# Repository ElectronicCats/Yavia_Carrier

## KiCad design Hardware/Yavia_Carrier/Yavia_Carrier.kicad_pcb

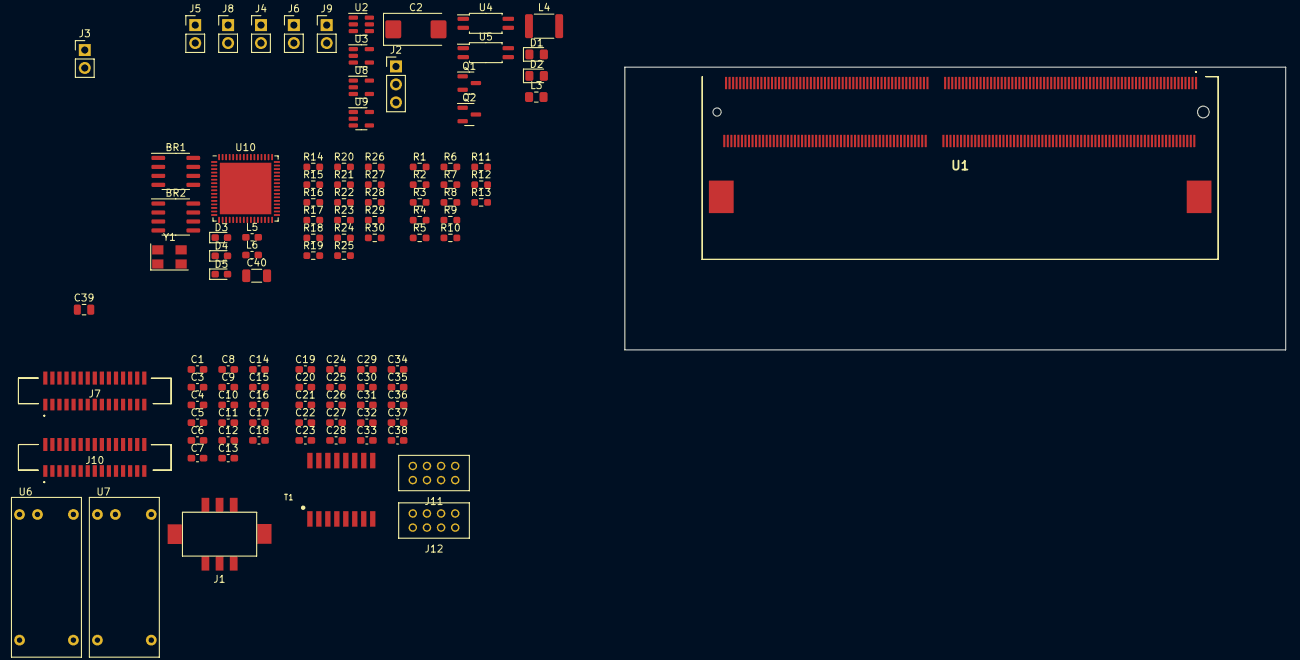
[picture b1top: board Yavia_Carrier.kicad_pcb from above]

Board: 2 copper layers, 93.5 x 40.0 mm, 107 parts (0 on the bottom side), 92 nets, no tracks yet.

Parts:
BR1, BR2: SP4031; SOIC-8_3.9x4.9mm_P1.27mm
C1, C3, C4, C5, C8, C11, C12: 22uF; C_0603_1608Metric_Pad1.08x0.95mm_HandSolder
C2: 220uF; CP_EIA-7343-31_Kemet-D_Pad2.25x2.55mm_HandSolder
C6, C7, C10: 10uF; C_0603_1608Metric_Pad1.08x0.95mm_HandSolder
C9: 100nF; C_0603_1608Metric_Pad1.08x0.95mm_HandSolder
C13, C14, C15, C16, C17, C18, C19, C21, C22, C23, C24, C25, C26, C28, C29, C31, C32, C33, C35, C36, C38: 0.1uF; C_0603_1608Metric_Pad1.08x0.95mm_HandSolder
C20: 4.7uF; C_0603_1608Metric_Pad1.08x0.95mm_HandSolder
C27, C34: 33pF; C_0603_1608Metric_Pad1.08x0.95mm_HandSolder
C30: 0.01uF; C_0603_1608Metric_Pad1.08x0.95mm_HandSolder
C37: 1uF; C_0603_1608Metric_Pad1.08x0.95mm_HandSolder
C39: 0.022uF; C_0805_2012Metric
C40: 1000pF; C_1206_3216Metric
D1: 5v; LED_0805_2012Metric_Pad1.15x1.40mm_HandSolder
D2: User; LED_0805_2012Metric_Pad1.15x1.40mm_HandSolder
D3, D4, D5: LED_Small; LED_0603_1608Metric_Pad1.05x0.95mm_HandSolder
J1: Power; DF11CZ-6DP-2V
J2: Serial; PinHeader_1x03_P2.54mm_Vertical
J3, J4: STRB_IS; PinHeader_1x02_P2.54mm_Vertical
J5, J6: STRB; PinHeader_1x02_P2.54mm_Vertical
J7, J10: 52610-1572; 526101572
J8, J9: FLASH; PinHeader_1x02_P2.54mm_Vertical
J11: USB; DF11-8DP-2DSA(08)
J12: Ethernet; DF11-8DP-2DSA(08)
L3: 2.2uH; L_0805_2012Metric_Pad1.15x1.40mm_HandSolder
L4: 3.9uH; L_1812_4532Metric
L5, L6: 2A_120R_100MHz; L_0603_1608Metric_Pad1.05x0.95mm_HandSolder
Q1, Q2: MMBT2222ALT1G; SOT-23
R1, R3, R6, R7, R10, R11, R16, R17, R18: 1K; R_0603_1608Metric_Pad0.98x0.95mm_HandSolder
R2: 10m; R_0603_1608Metric_Pad0.98x0.95mm_HandSolder
R4, R5: 4.7K; R_0603_1608Metric_Pad0.98x0.95mm_HandSolder
R8, R9: 500K; R_0603_1608Metric_Pad0.98x0.95mm_HandSolder
R12, R13, R14, R19, R23: 10K; R_0603_1608Metric_Pad0.98x0.95mm_HandSolder
R15: 1M; R_0603_1608Metric_Pad0.98x0.95mm_HandSolder
R20: 10R; R_0603_1608Metric_Pad0.98x0.95mm_HandSolder
R21, R22, R26, R28: 50R; R_0603_1608Metric_Pad0.98x0.95mm_HandSolder
R24: 12.0K 1/10W; R_0603_1608Metric_Pad0.98x0.95mm_HandSolder
R25: 825 1/10W; R_0603_1608Metric_Pad0.98x0.95mm_HandSolder
R27: 12.4K; R_0603_1608Metric_Pad0.98x0.95mm_HandSolder
R29, R30: 75R; R_0603_1608Metric_Pad0.98x0.95mm_HandSolder
T1: HX1188NL; HXXXX
U1: Verdin iMX8M Plus; 23094092
U2: AP63203; TSOT-23-6
U3: LM3671; SOT-23-5
U4, U5: TCMT1103; SOP-4_4.4x2.6mm_P1.27mm
U6, U7: LDD600L; LDD-L
U8, U9: 74AHC1G32; SOT-23-5
U10: LAN9512i; QFN-64-1EP_9x9mm_P0.5mm_EP7.3x7.3mm
Y1: 25MHZ; Crystal_SMD_5032-4Pin_5.0x3.2mm

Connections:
+1V8: C10.1, C14.1, L3.2, U3.4 (ADJ)
+3V3: C11.1, C12.1, C13.1, C15.1, C17.1, C18.1, C19.1, C21.1, C24.1, C28.1, C32.1, D1.2 (A), J7.1, J7.2, J10.1, L4.2, L5.1, R4.2, R5.2, R8.1, R9.1, R14.2, R16.1, R17.1, R18.1, R19.2, R23.2, R25.2, U2.1 (FB), U8.5 (VCC), U9.5 (VCC), U10.19 (VDD33IO), U10.27 (VDD33IO), U10.28 (~TRST), U10.29 (TMS), U10.30 (TDI), U10.33 (VDD33IO), U10.39 (VDD33IO), U10.40 (TEST3), U10.46 (VDD33IO)
+5V: C2.1, C6.1, C7.1, C16.1, J1.5, J11.2, J11.4, U2.2 (EN), U2.3 (VIN), U3.1 (VIN), U3.3 (EN)
+12V: J1.1, R12.1, R13.1, U6.1 (VIN+), U7.1 (VIN+)
+36V: J8.1, J9.1, U6.6 (+VOUT), U7.6 (+VOUT)
/CAM0_CLK+: J10.13, U1.162 (CSI2_CLK_P)
/CAM0_CLK-: J10.15, U1.160 (CSI2_CLK_N)
/CAM0_D0+: J10.25, U1.150 (CSI2_D0_P)
/CAM0_D0-: J10.27, U1.148 (CSI2_D0_N)
/CAM0_D1+: J10.19, U1.156 (CSI2_D1_P)
/CAM0_D1-: J10.21, U1.154 (CSI2_D1_N)
/CAM0_IO0: J10.9, U1.216 (GPIO_5)
/CAM0_IO1: J10.7, U1.218 (GPIO_6)
/CAM0_SCL: J10.5, U1.14 (I2C_1_SCL)
/CAM0_SDA: J10.3, U1.12 (I2C_1_SDA)
/CAM1_CLK+: J7.13, J7.14, U1.111 (CSI_1_CLK_P)
/CAM1_CLK-: J7.15, J7.16, U1.113 (CSI_1_CLK_N)
/CAM1_D0+: J7.25, J7.26, U1.123 (CSI_1_D0_P)
/CAM1_D0-: J7.27, J7.28, U1.125 (CSI_1_D0_N)
/CAM1_D1+: J7.19, J7.20, U1.117 (CSI_1_D1_P)
/CAM1_D1-: J7.21, J7.22, U1.119 (CSI_1_D1_N)
/CAM1_IO0: J7.9, J7.10, U1.222 (GPIO_8)
/CAM1_IO1: J7.7, J7.8, U1.220 (GPIO_7)
/CAM1_SCL: J7.5, J7.6, R5.1, U1.93 (I2C_4_CSI_SDA)
/CAM1_SDA: J7.3, J7.4, R4.1, U1.95 (I2C_4_CSI_SCL)
/Flash_EN: U1.208 (GPIO_2), U8.2
/Flash_EN_1: U1.210 (GPIO_3), U9.2
/LDD_OUT: Q1.3 (C), R12.2, U6.3 (PWM)
/LDD_OUT_1: Q2.3 (C), R13.2, U7.3 (PWM)
/LED_R: D2.2 (A), U1.206 (GPIO_1)
/RX_UART: J2.2, U1.129 (UART_1_RXD)
/TX_UART: J2.1, U1.131 (UART_1_TXD)
/USB_ETHERNET/DRx+: J12.3, T1.11
/USB_ETHERNET/DRx-: J12.1, T1.9
/USB_ETHERNET/DS1_D+: J11.5, U10.2 (USBDP2)
/USB_ETHERNET/DS1_D-: J11.7, U10.1 (USBDM2)
/USB_ETHERNET/DS2_D+: J11.1, U10.4 (USBDP3)
/USB_ETHERNET/DS2_D-: J11.3, U10.3 (USBDM3)
/USB_ETHERNET/DTx+: J12.7, T1.16
/USB_ETHERNET/DTx-: J12.5, T1.14
/USB_ETHERNET/LED_FDX: D5.1 (K), U10.20 (~FDX_LED/GPIO0)
/USB_ETHERNET/LNKA_LED: D4.1 (K), U10.21 (~LNKA_LED/GPIO1)
/USB_ETHERNET/ORx+: BR1.5 (OUT), U10.52 (RXP)
/USB_ETHERNET/ORx-: BR1.8 (OUT), U10.53 (RXN)
/USB_ETHERNET/OTx+: BR2.5 (OUT), U10.55 (TXP)
/USB_ETHERNET/OTx-: BR2.8 (OUT), U10.56 (TXN)
/USB_ETHERNET/RST: C30.1, R14.1, U10.12 (~RESET)
/USB_ETHERNET/RX+: BR1.4 (IN), R26.1, T1.6
/USB_ETHERNET/RX-: BR1.1 (IN), R28.1, T1.8
/USB_ETHERNET/SPD_LED: D3.1 (K), U10.22 (~SPD_LED/GPIO2)
/USB_ETHERNET/TX+: BR2.4 (IN), R21.1, T1.1
/USB_ETHERNET/TX-: BR2.1 (IN), R22.1, T1.3
/USB_ETHERNET/VDD18: C20.1, C23.1, C26.1, U10.15 (VDD18CORE), U10.38 (VDD18CORE)
/USB_ETHERNET/VDD18E: C33.1, L6.1, U10.48 (VDD18ETHPLL)
/USB_ETHERNET/VDD18U: C37.1, L6.2, U10.62 (VDD18USBPLL)
/USB_ETHERNET/VDD33A: C22.1, C25.1, C29.1, C31.1, C35.1, C36.1, C38.1, L5.2, R20.2, R21.2, R22.2, R26.2, R28.2, U10.5 (VDD33A), U10.10 (VDD33A), U10.49 (VDD33A), U10.51 (VDD33A), U10.54 (VDD33A), U10.57 (VDD33A), U10.64 (VDD33A)
/USB_ETHERNET/XI: C27.1, R15.2, U10.61 (XI), Y1.1
/USB_ETHERNET/XO: C34.1, R15.1, U10.60 (XO), Y1.3
/VT: C1.1, C3.1, C4.1, C5.1, C8.1, R2.2, U1.251 (VCC), U1.253 (VCC), U1.255 (VCC), U1.257 (VCC), U1.259 (VCC)
/opto_out: J3.2, R8.2, U4.4, U8.1
/opto_out_1: J4.2, R9.2, U5.4, U9.1
GND: C1.2, C2.2, C3.2, C4.2, C5.2, C6.2, C7.2, C8.2, C10.2, C11.2, C12.2, C13.2, C14.2, C15.2, C16.2, C17.2, C18.2, C19.2, C20.2, C21.2, C22.2, C23.2, C24.2, C25.2, C26.2, C27.2, C28.2, C29.2, C30.2, C31.2, C32.2, C33.2, C34.2, C35.2, C36.2, C37.2, C38.2, C39.2, C40.2, J1.2, J1.3, J1.4, J1.6, J2.3, J3.1, J4.1, J7.11, J7.12, J7.17, J7.18, J7.23, J7.24, J7.29, J7.30, J10.11, J10.17, J10.23, J10.29, J11.6, J11.8, Q1.2 (E), Q2.2 (E), R1.2, R3.2, R24.2, R27.2, U1.10 (GND), U1.11 (GND), U1.18 (GND), U1.27 (GND), U1.28 (GND), U1.33 (GND), U1.39 (GND), U1.40 (GND), U1.45 (GND), U1.50 (GND), U1.51 (GND), U1.65 (GND), U1.68 (GND), U1.71 (GND), U1.77 (GND), U1.83 (GND), U1.86 (GND), U1.89 (GND), U1.97 (GND), U1.98 (GND), U1.103 (GND), U1.109 (GND), U1.110 (GND), U1.115 (GND), U1.121 (GND), U1.122 (GND), U1.127 (GND), U1.134 (GND), U1.145 (GND), U1.146 (GND), U1.158 (GND), U1.167 (GND), U1.170 (GND), U1.173 (GND), U1.179 (GND), U1.182 (GND), U1.194 (GND), U1.195 (GND), U1.204 (GND), U1.209 (GND), U1.223 (GND), U1.224 (GND), U1.229 (GND), U1.230 (GND), U1.236 (GND), U1.242 (GND), U1.243 (GND), U2.4 (GND), U3.2 (GND), U4.3, U5.3, U6.4 (VIN-), U7.4 (VIN-), U8.3 (GND), U9.3 (GND), U10.34 (TEST2), U10.44 (CLK24_EN), U10.65 (GND), Y1.2, Y1.4
GNDPWR: J8.2, J9.2, U6.5 (-VOUT), U7.5 (-VOUT)
unnamed: C39.1, R20.1, T1.2, T1.7
unnamed: C40.1, R29.1, R30.1
unnamed: D1.1 (K), R1.1
unnamed: D2.1 (K), R3.1
unnamed: D3.2 (A), R16.2
unnamed: D4.2 (A), R17.2
unnamed: D5.2 (A), R18.2
unnamed: J5.1, R6.2
unnamed: J5.2, U4.1
unnamed: J6.1, R7.2
unnamed: J6.2, U5.1
unnamed: Q1.1 (B), R10.1
unnamed: Q2.1 (B), R11.1
unnamed: R6.1, U4.2
unnamed: R7.1, U5.2
unnamed: R10.2, U8.4
unnamed: R11.2, U9.4
unnamed: R29.2, T1.10
unnamed: R30.2, T1.15
unnamed: C9.2, U2.6 (BST)
unnamed: C9.1, L4.1, U2.5 (SW)
unnamed: L3.1, U3.5 (VOUT)
unnamed: R19.1, U10.32 (TCK)
unnamed: R23.1, U10.41 (AUTOMDIX_EN)
unnamed: R27.1, U10.50 (EXRES)
unnamed: R24.1, U10.63 (USBRBIAS)
unnamed: R25.1, U10.11 (VBUS_DET)
UP-D+: U1.165 (USB_1_D_P), U10.59 (USBDP0)
UP-D-: U1.163 (USB_1_D_N), U10.58 (USBDM0)

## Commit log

2023-05-12 init schematic yavia gnd
2023-05-17 add one MIPI CSI connection
2023-05-18 add MIPI SCI and power supply connections,
2023-05-18 add ldd circuit
2023-06-12 Fix U1 symbol & started pcb
2023-06-13 start of component arrangement & add 3d models
